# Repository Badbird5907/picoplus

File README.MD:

# Pico+
[Video Demo](https://www.youtube.com/shorts/jsLF4tYyZew)

This is my take on the Raspberry Pi Pico 2. It features:
- RP2350A
- USB C
- A very stable 3.3V power supply (TPS7A20)
- A WS2812 LED
- A reset button (!!!)
- Large SPI flash on SPI0
- Large PSRAM chip on SPI1

I wanted to make this project as the stock pico is kinda underpowered, and I wanted to make a overkill version. While making this project, I did have to reduce my scope by removing the I2C EEPROM and some other features. However, I'm really happy with the resulting board.

# BOM
Note: this is more or less a direct export of my LCSC cart. Most parts have a minimum order quantity, hence the large quantities. 

|Name                  |Description                                                                                                                               |Quantity|Unit Price($)|Total (USD)|
|----------------------|------------------------------------------------------------------------------------------------------------------------------------------|--------|-------------|-----------|
|0402WGF1001TCE        |62.5mW Thick Film Resistor 50V ±100ppm/℃ ±1% 1kΩ 0402 Chip Resistor - Surface Mount ROHS                                                  |100     |0.0006       |0.06       |
|0402CG150J500NT       |50V 15pF C0G ±5% 0402 Multilayer Ceramic Capacitors MLCC - SMD/SMT ROHS                                                                   |100     |0.001        |0.1        |
|CC0201KRX5R6BB104     |10V 100nF X5R ±10% 0201 Multilayer Ceramic Capacitors MLCC - SMD/SMT ROHS                                                                 |100     |0.0011       |0.11       |
|W25Q128JVPIQ          |SPI 133MHz WSON-8-EP(5x6) NOR FLASH ROHS                                                                                                  |1       |0.9177       |0.92       |
|ABM8-272-T3           |SMD3225-4P Crystals ROHS                                                                                                                  |1       |0.3731       |0.37       |
|0603WAF100KT5E        |100mW Thick Film Resistor 75V ±1% ±400ppm/℃ 1Ω 0603 Chip Resistor - Surface Mount ROHS                                                    |100     |0.0016       |0.16       |
|KT-0805G              |Emerald Green 0805 LED Indication - Discrete ROHS                                                                                         |50      |0.011        |0.55       |
|CL05A475MP5NRNC       |10V 4.7uF X5R ±20% 0402 Multilayer Ceramic Capacitors MLCC - SMD/SMT ROHS                                                                 |50      |0.0052       |0.26       |
|0402WGF2000TCE        |62.5mW Thick Film Resistor 50V ±100ppm/℃ ±1% 200Ω 0402 Chip Resistor - Surface Mount ROHS                                                 |100     |0.0006       |0.06       |
|0402WGF330JTCE        |62.5mW Thick Film Resistor 50V ±100ppm/℃ ±1% 33Ω 0402 Chip Resistor - Surface Mount ROHS                                                  |100     |0.0006       |0.06       |
|0402WGF4700TCE        |62.5mW Thick Film Resistor 50V ±100ppm/℃ ±1% 470Ω 0402 Chip Resistor - Surface Mount ROHS                                                 |100     |0.0006       |0.06       |
|0402WGF1002TCE        |62.5mW Thick Film Resistor 50V ±100ppm/℃ ±1% 10kΩ 0402 Chip Resistor - Surface Mount ROHS                                                 |100     |0.0006       |0.06       |
|0402WGF5101TCE        |62.5mW Thick Film Resistor 50V ±100ppm/℃ ±1% 5.1kΩ 0402 Chip Resistor - Surface Mount ROHS                                                |100     |0.0005       |0.05       |
|TYPE-C 16PIN 2MD(073) |3A USB 3.1 1 Surface Mount, Right Angle 16P Female -25℃~+85℃ Type-C SMD USB Connectors ROHS                                               |10      |0.0549       |0.55       |
|XL-5050RGBC-WS2812B   |SMD5050 RGB LEDs(Built-in IC) ROHS                                                                                                        |10      |0.049        |0.49       |
|TPS7A2033PDBVR        |65dB@(100kHz) 300mA Fixed 3.3V Positive 6V SOT-23-5 Voltage Regulators - Linear, Low Drop Out (LDO) Regulators ROHS                       |5       |0.2081       |1.04       |
|APS6404L-3SQR-ZR      |USON-8L DRAM ROHS                                                                                                                         |1       |1.1433       |1.14       |
|RP2350A               |QFN-60-EP(7x7) Microcontrollers (MCU/MPU/SOC) ROHS                                                                                        |5       |1.6544       |1.6544       |
|AOTA-B201610S3R3-101-T|0806 Power Inductors ROHS                                                                                                                 |5       |0.2584       |1.29       |
|0201WMF270JTEE        |50mW Thick Film Resistor 25V ±1% ±200ppm/℃ 27Ω 0201 Chip Resistor - Surface Mount ROHS                                                    |100     |0.0008       |0.08       |
|TS-1088-AR02016       |Without Bracket 50mA 4mm 100,000 Cycles 12V 1.6N 3mm 2mm Round Button Surface Mount,Vertical SPST SMD Tactile Switches ROHS               |10      |0.0434       |0.43       |
|B5819W SL             |40V 600mV@1A 1A SOD-123 Schottky Diodes ROHS                                                                                              |20      |0.0233       |0.47       |
|LCSC Shipping         |                                                                                                                                          |        |             |12.12      |
|PCB                   |                                                                                                                                          |        |             |56.1       |
|Stencil               |                                                                                                                                          |        |             |7          |
|JLC Shipping          |                                                                                                                                          |        |             |7.78       |
|                      |                                                                                                                                          |        |             |           |
|TOTAL                 |                                                                                                                                          |        |             |92.9644     |

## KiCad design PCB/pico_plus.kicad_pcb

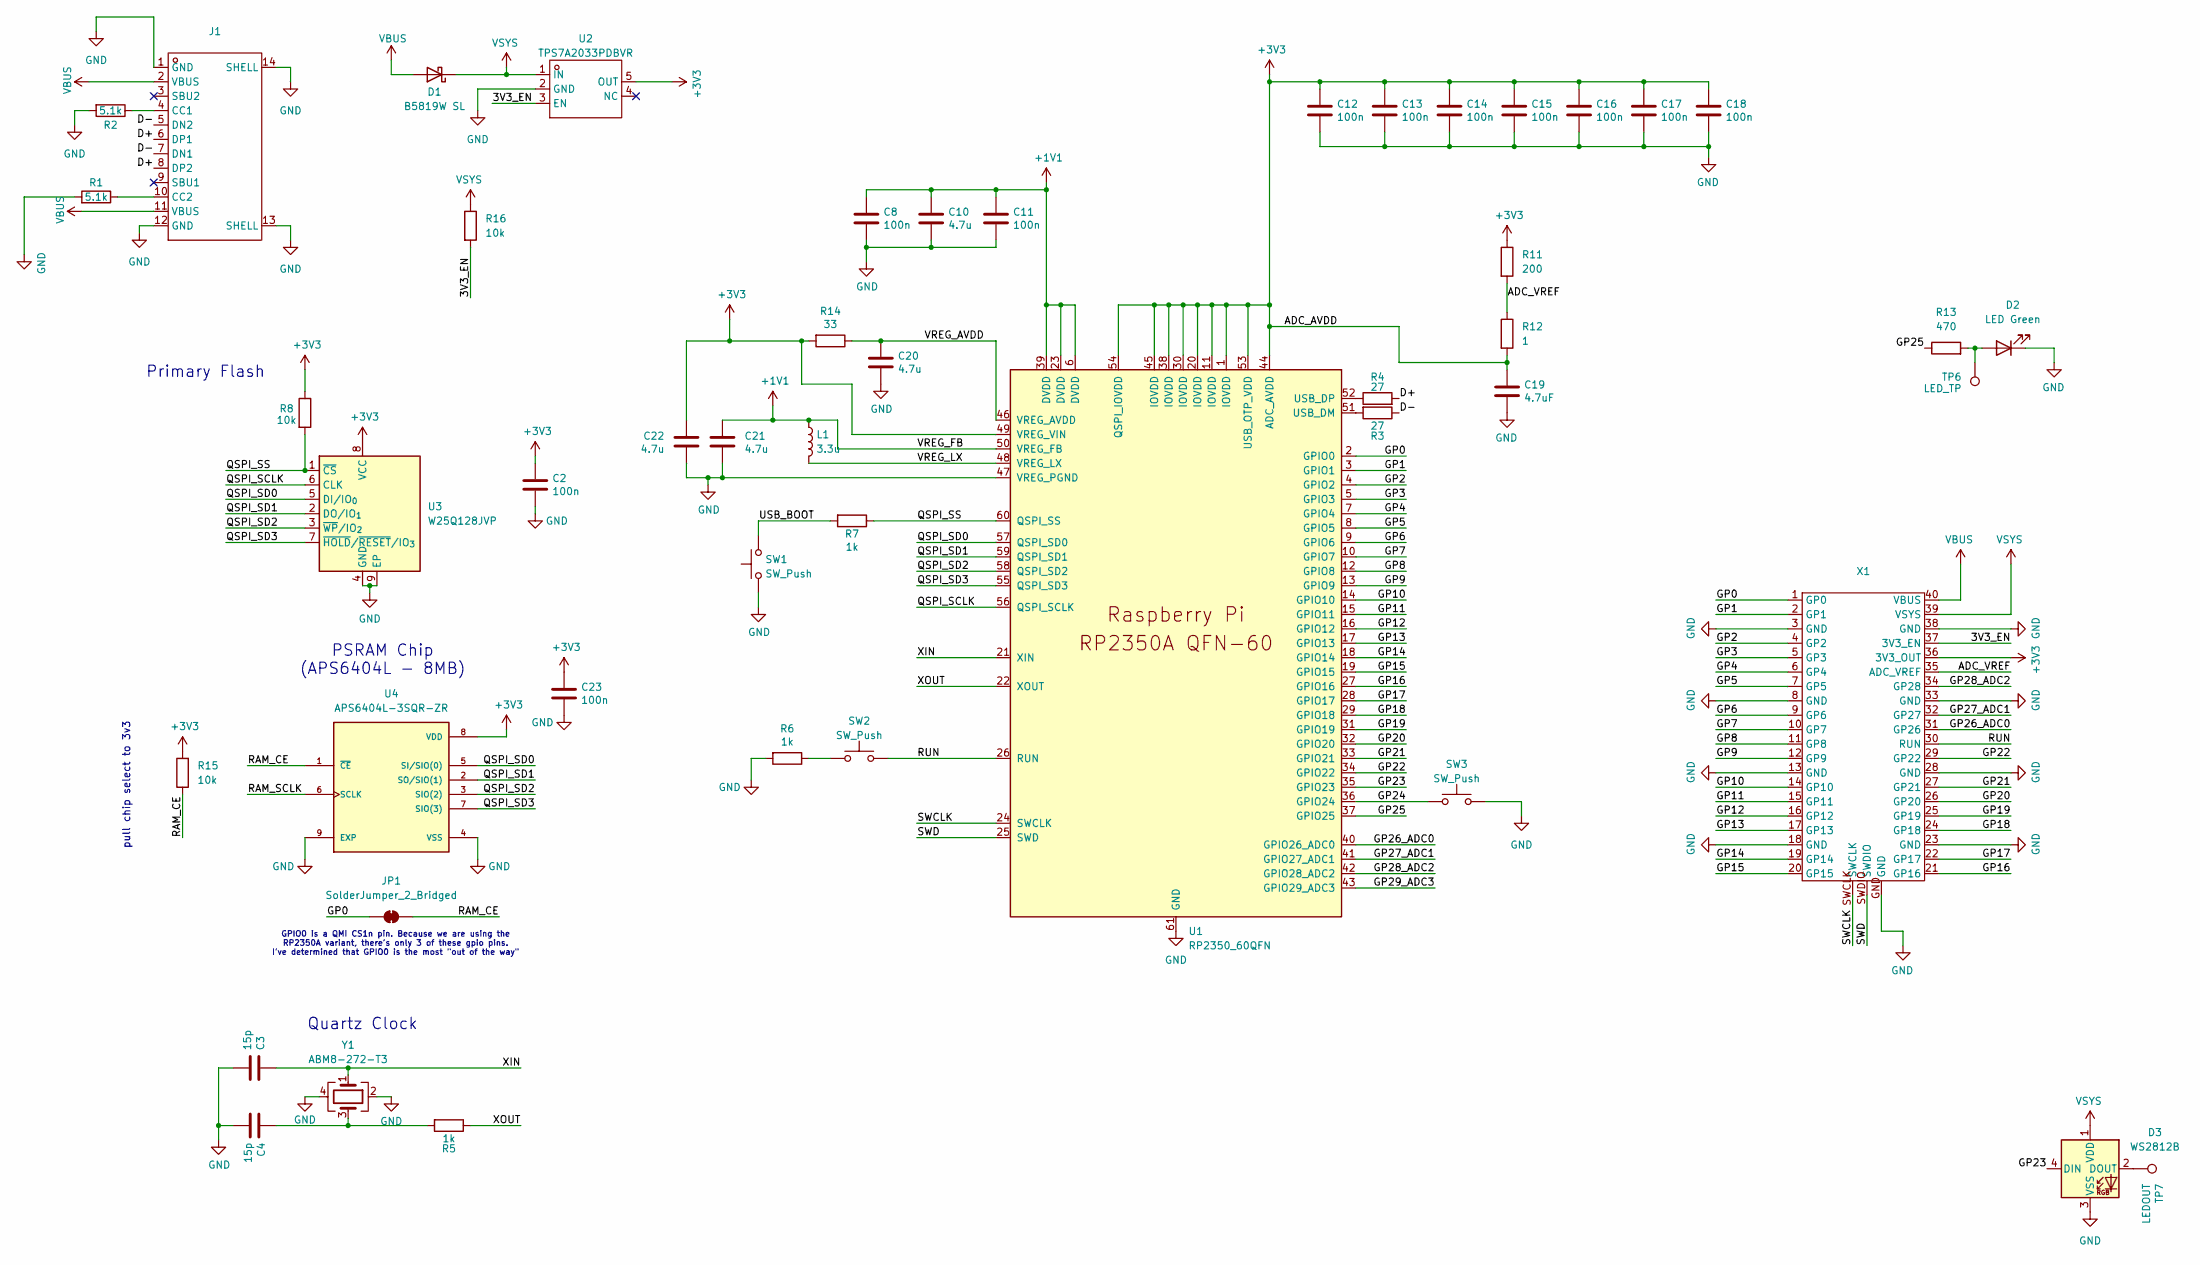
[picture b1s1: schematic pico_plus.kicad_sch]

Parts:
C2, C8, C11, C12, C13, C14, C15, C16, C17, C18, C23: 100n; C_0201_0603Metric
C3, C4: 15p; C_0402_1005Metric
C10, C20: 4.7u; C_0402_1005Metric
C19: 4.7uF; C_0402_1005Metric
C21, C22: 4.7u; C_0402_1005Metric_small_pads
D1: B5819W SL; D_SOD-123
D2: LED Green; LED_0805_2012Metric
D3: WS2812B; LED_WS2812B_PLCC4_5.0x5.0mm_P3.2mm
J1: USB-C-SMD_TYPE-C-6PIN-2MD-073; Manufacturer Part TYPE-C 16PIN 2MD(073); LCSC Part Name Type-C 母 卧贴
JP1: SolderJumper_2_Bridged; SolderJumper-2_P1.3mm_Bridged2Bar_RoundedPad1.0x1.5mm
L1: 3.3u; L_pol_2016
R1, R2: 5.1k; R_0402_1005Metric
R3, R4: 27; R_0201_0603Metric
R5, R6, R7: 1k; R_0402_1005Metric
R8, R15, R16: 10k; R_0402_1005Metric
R11: 200; R_0402_1005Metric
R12: 1; R_0603_1608Metric
R13: 470; R_0402_1005Metric
R14: 33; R_0402_1005Metric
SW1, SW2, SW3: SW_Push; SW-SMD_L3.9-W3.0-P4.45
TP6: LED_TP; TestPoint_Pad_D1.0mm
TP7: LEDOUT; TestPoint_Pad_D1.0mm
U1: RP2350_60QFN; RP2350-QFN-60-1EP_7x7_P0.4mm_EP3.4x3.4mm_ThermalVias
U2: TPS7A2033PDBVR; SOT-23-5_L2.9-W1.6-P0.95-LS2.8-BR; Manufacturer Part TPS7A2033PDBVR; LCSC Part Name 具有高 PSRR 的 300mA、超低噪声、低 IQ、低压降 (LDO) 线性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
U3: W25Q128JVP; WSON-8-1EP_6x5mm_P1.27mm_EP3.4x4.3mm
U4: APS6404L-3SQR-ZR; PSON50P200X300X50-9N; PARTREV 2.3
X1: Pico_Castellated_Holes
Y1: ABM8-272-T3; XTAL_ABM8-272-T3

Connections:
+1V1: C8.1, C10.1, C11.1, C21.1, L1.1, U1.6 (DVDD), U1.23 (DVDD), U1.39 (DVDD), U1.50 (VREG_FB)
+3V3: C2.1, C12.1, C13.1, C14.1, C15.1, C16.1, C17.1, C18.1, C19.1, C22.1, C23.1, R8.1, R11.1, R12.2, R14.2, R15.2, U1.1 (IOVDD), U1.11 (IOVDD), U1.20 (IOVDD), U1.30 (IOVDD), U1.38 (IOVDD), U1.44 (ADC_AVDD), U1.45 (IOVDD), U1.49 (VREG_VIN), U1.53 (USB_OTP_VDD), U1.54 (QSPI_IOVDD), U2.5 (OUT), U3.8 (VCC), U4.8 (VDD), X1.36 (3V3_OUT)
/3V3_EN: R16.2, U2.3 (EN), X1.37 (3V3_EN)
/ADC_VREF: R11.2, R12.1, X1.35 (ADC_VREF)
/D+: J1.6 (DP1), J1.8 (DP2), R4.2
/D-: J1.5 (DN2), J1.7 (DN1), R3.1
/GP0: JP1.1 (A), U1.2 (GPIO0), X1.1 (GP0)
/GP1: U1.3 (GPIO1), X1.2 (GP1)
/GP2: U1.4 (GPIO2), X1.4 (GP2)
/GP3: U1.5 (GPIO3), X1.5 (GP3)
/GP4: U1.7 (GPIO4), X1.6 (GP4)
/GP5: U1.8 (GPIO5), X1.7 (GP5)
/GP6: U1.9 (GPIO6), X1.9 (GP6)
/GP7: U1.10 (GPIO7), X1.10 (GP7)
/GP8: U1.12 (GPIO8), X1.11 (GP8)
/GP9: U1.13 (GPIO9), X1.12 (GP9)
/GP10: U1.14 (GPIO10), X1.14 (GP10)
/GP11: U1.15 (GPIO11), X1.15 (GP11)
/GP12: U1.16 (GPIO12), X1.16 (GP12)
/GP13: U1.17 (GPIO13), X1.17 (GP13)
/GP14: U1.18 (GPIO14), X1.19 (GP14)
/GP15: U1.19 (GPIO15), X1.20 (GP15)
/GP16: U1.27 (GPIO16), X1.21 (GP16)
/GP17: U1.28 (GPIO17), X1.22 (GP17)
/GP18: U1.29 (GPIO18), X1.24 (GP18)
/GP19: U1.31 (GPIO19), X1.25 (GP19)
/GP20: U1.32 (GPIO20), X1.26 (GP20)
/GP21: U1.33 (GPIO21), X1.27 (GP21)
/GP22: U1.34 (GPIO22), X1.29 (GP22)
/GP23: D3.4 (DIN), U1.35 (GPIO23)
/GP24: SW3.1, U1.36 (GPIO24)
/GP25: R13.1, U1.37 (GPIO25)
/GP26_ADC0: U1.40 (GPIO26_ADC0), X1.31 (GP26)
/GP27_ADC1: U1.41 (GPIO27_ADC1), X1.32 (GP27)
/GP28_ADC2: U1.42 (GPIO28_ADC2), X1.34 (GP28)
/GP29_ADC3: U1.43 (GPIO29_ADC3)
/QSPI_SCLK: U1.56 (QSPI_SCLK), U3.6 (CLK)
/QSPI_SD0: U1.57 (QSPI_SD0), U3.5 (DI/IO_{0}), U4.5 (SI/SIO(0))
/QSPI_SD1: U1.59 (QSPI_SD1), U3.2 (DO/IO_{1}), U4.2 (SO/SIO(1))
/QSPI_SD2: U1.58 (QSPI_SD2), U3.3 (~WP/IO_{2}), U4.3 (SIO(2))
/QSPI_SD3: U1.55 (QSPI_SD3), U3.7 (~HOLD/~RESET/IO_{3}), U4.7 (SIO(3))
/QSPI_SS: R7.1, R8.2, U1.60 (QSPI_SS), U3.1 (~CS)
/RAM_CE: JP1.2 (B), R15.1, U4.1 (~CE)
/RAM_SCLK: U4.6 (SCLK)
/RUN: SW2.2, U1.26 (RUN), X1.30 (RUN)
/SWCLK: U1.24 (SWCLK), X1.SWCLK
/SWD: U1.25 (SWD), X1.SWDIO
/USB_BOOT: R7.2, SW1.2
/VREG_AVDD: C20.1, R14.1, U1.46 (VREG_AVDD)
/VREG_LX: L1.2, U1.48 (VREG_LX)
/XIN: C3.1, U1.21 (XIN), Y1.1
/XOUT: R5.1, U1.22 (XOUT)
GND: C2.2, C3.2, C4.2, C8.2, C10.2, C11.2, C12.2, C13.2, C14.2, C15.2, C16.2, C17.2, C18.2, C19.2, C20.2, C21.2, C22.2, C23.2, D2.1 (K), D3.3 (VSS), J1.1 (GND), J1.12 (GND), J1.13 (SHELL), J1.14 (SHELL), R1.2, R2.2, R6.2, SW1.1, SW3.2, U1.47 (VREG_PGND), U1.61 (GND), U2.2 (GND), U3.4 (GND), U3.9 (EP), U4.4 (VSS), U4.9 (EXP), X1.3 (GND), X1.8 (GND), X1.13 (GND), X1.18 (GND), X1.23 (GND), X1.28 (GND), X1.33 (GND), X1.38 (GND), X1.GND, Y1.2, Y1.4
unnamed: C4.1, R5.2, Y1.3
unnamed: D2.2 (A), R13.2, TP6.1
unnamed: D3.2 (DOUT), TP7.1
unnamed: J1.4 (CC1), R2.1
unnamed: J1.10 (CC2), R1.1
unnamed: R6.1, SW2.1
unnamed: R3.2, U1.51 (USB_DM)
unnamed: R4.1, U1.52 (USB_DP)
VBUS: D1.2 (A), J1.2 (VBUS), J1.11 (VBUS), X1.40 (VBUS)
VSYS: D1.1 (K), D3.1 (VDD), R16.1, U2.1 (IN), X1.39 (VSYS)

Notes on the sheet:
Primary Flash
Quartz Clock
PSRAM Chip (APS6404L - 8MB)
pull chip select to 3v3
GPIO0 is a QMI CS1n pin. Because we are using the RP2350A variant, there's only 3 of these gpio pins. I've determined that GPIO0 is the most "out of the way"

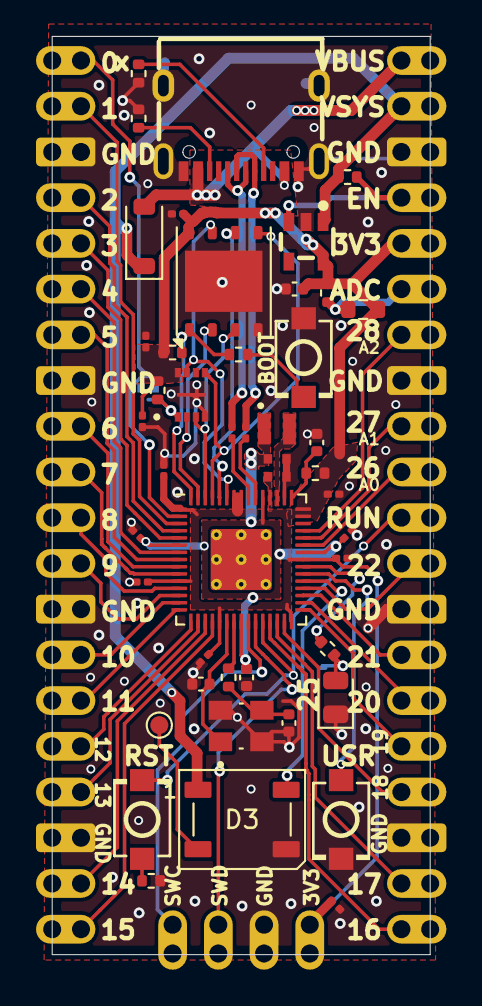
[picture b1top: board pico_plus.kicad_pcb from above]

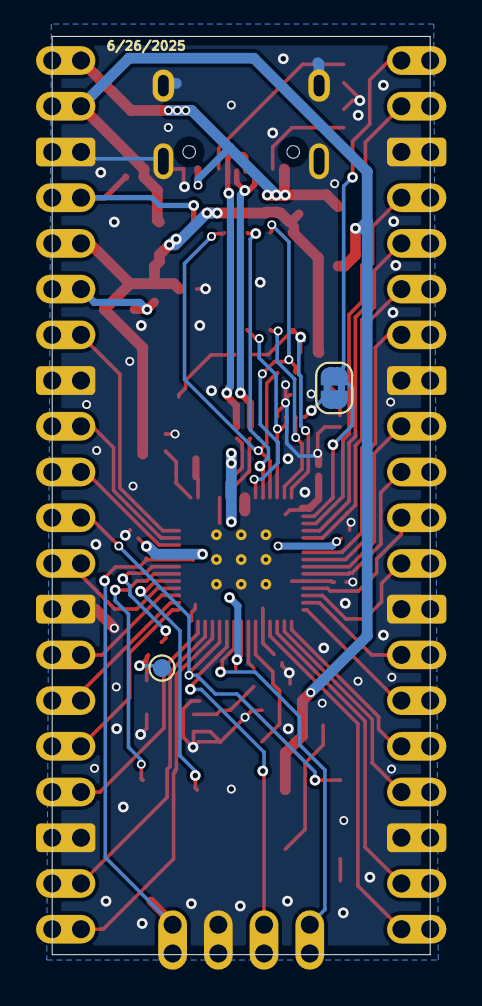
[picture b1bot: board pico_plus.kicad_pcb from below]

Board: 2 copper layers, 21.0 x 51.0 mm, 49 parts (2 on the bottom side), 61 nets.

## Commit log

2025-06-21 Some work on schematic
2025-06-22 journal
2025-06-22 lockfile
2025-06-22 a lot of work
2025-06-23 finish schematic
2025-06-24 work on pcb
2025-06-25 temp
2025-06-25 finish routing
2025-06-25 finish pcb
2025-06-26 schematic fix
2025-06-26 finish up pcb + bom
2025-06-26 readme
2025-06-27 update bom
2025-06-28 forgot bom.csv
2025-06-28 total hrs
2026-01-28 Update images in README
    Updated PCB image link and added schematic image.
